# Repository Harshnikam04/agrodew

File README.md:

<div align="center">
  <h1>🌱 Agrodew</h1>
  <p>An end-to-end smart agriculture system combining custom IoT hardware, a powerful backend, and a cross-platform mobile application.</p>

  <p>

  </p>
</div>

---

## 📖 Overview

**Agrodew** is a comprehensive solution designed to monitor and manage agricultural data. By deploying custom hardware sensors in the field, data is transmitted to a central backend and displayed in real-time on a mobile application. This empowers farmers and agricultural enthusiasts to make data-driven decisions based on live environmental metrics.

## 🏗️ System Architecture (Monorepo)

This repository contains all three core components of the Agrodew ecosystem:

### 1. `mobile/` 📱
The user-facing mobile application built to provide real-time analytics and controls.
- **Features**: Interactive dashboards, real-time sensor updates, and AI-driven insights (`aiService.js`).
- **Tech**: React Native / Expo.

### 2. `backend/` ⚙️
The core API server that bridges the hardware and the mobile application.
- **Features**: REST API endpoints for receiving data from Arduino/IoT devices, processing sensor readings (Temperature, Humidity, Soil Moisture, Water Level, AQI), and storing them in a Firebase Firestore database.
- **Tech**: Node.js, Express, Firebase Admin SDK.

### 3. `agrodewpcb/` ⚡
The custom-designed Printed Circuit Board (PCB) for data collection.
- **Features**: Integrates multiple sensors and a microcontroller into a single, deployable field unit.
- **Tech**: KiCad 9.0 (Schematics and PCB layouts included).

---

## 🚀 Key Features

- **Real-Time Environmental Monitoring**: Track Temperature, Humidity, Soil Moisture, Water Levels, and Air Quality Index (AQI).
- **IoT Integration**: Direct communication between custom hardware nodes and the cloud backend.
- **AI Analytics**: Intelligent data processing integrated directly into the mobile client.
- **Cloud Database**: Fast, scalable, and secure data storage using Firebase.

---

## 🛠️ Getting Started

To run the project locally, you will need to start both the backend and the mobile app.

### Backend Setup
1. Navigate to the backend directory:
   ```bash
   cd backend
   ```
2. Install dependencies:
   ```bash
   npm install
   ```
3. Ensure you have your Firebase Service Account credentials set up.
4. Start the server:
   ```bash
   npm run dev
   ```

### Mobile Setup
1. Open a new terminal and navigate to the mobile directory:
   ```bash
   cd mobile
   ```
2. Install dependencies:
   ```bash
   npm install
   ```
3. Start the application:
   ```bash
   npm start
   ```

---

## 🤝 Contributing

Contributions are always welcome! Feel free to open an issue or submit a Pull Request if you have suggestions for new features or improvements.

## 📄 License

This project is open-source and available under the [MIT License](LICENSE).

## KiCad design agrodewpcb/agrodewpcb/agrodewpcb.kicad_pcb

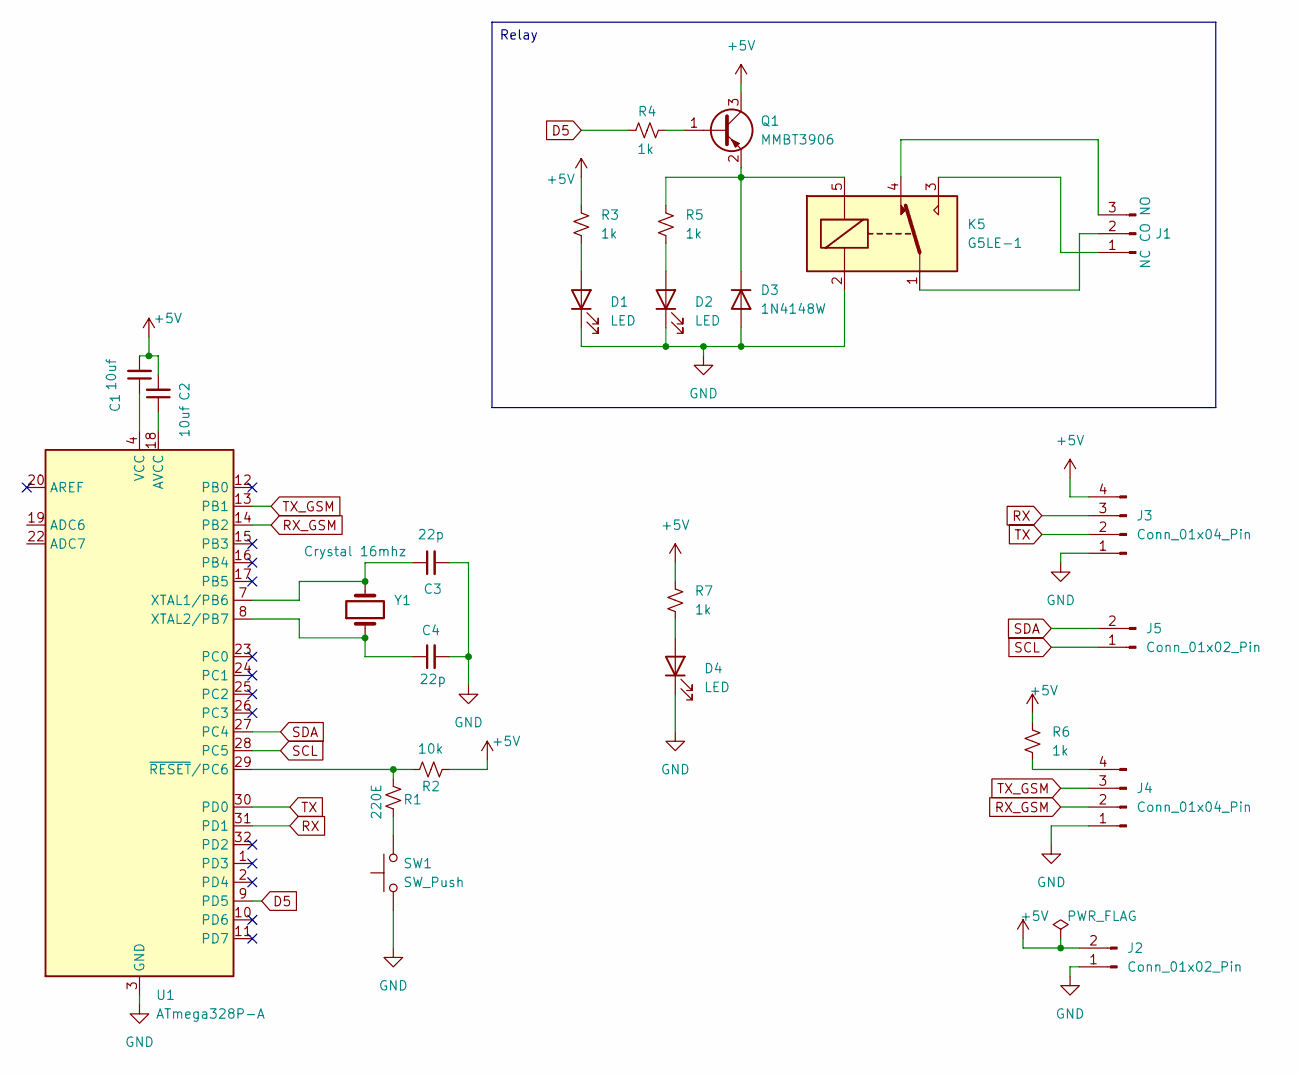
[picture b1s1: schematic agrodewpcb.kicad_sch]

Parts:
C1, C2: 10uf; C_1206_3216Metric_Pad1.33x1.80mm_HandSolder
C3, C4: 22p; C_1206_3216Metric_Pad1.33x1.80mm_HandSolder
D1, D2, D4: LED; LED_1206_3216Metric_Pad1.42x1.75mm_HandSolder
D3: 1N4148W; D_SOD-123
J1: NC CO NO; JST_NV_B03P-NV_1x03_P5.00mm_Vertical
J2, J5: Conn_01x02_Pin; PinHeader_1x02_P2.54mm_Vertical
J3, J4: Conn_01x04_Pin; PinHeader_1x04_P2.54mm_Vertical
K5: G5LE-1; Relay_SPDT_Omron-G5LE-1
Q1: MMBT3906; SOT-23
R1: 220E; R_1206_3216Metric_Pad1.30x1.75mm_HandSolder
R2: 10k; R_1206_3216Metric_Pad1.30x1.75mm_HandSolder
R3, R4, R5, R6, R7: 1k; R_1206_3216Metric_Pad1.30x1.75mm_HandSolder
SW1: SW_Push; SW_Push_1P1T_XKB_TS-1187A
U1: ATmega328P-A; TQFP-32_7x7mm_P0.8mm
Y1: Crystal 16mhz; Crystal_HC49-4H_Vertical

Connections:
+5V: C1.2, C2.2, J2.2, J3.4, Q1.3 (C), R2.2, R3.1, R6.1, R7.1
D5: R4.1, U1.9 (PD5)
GND: C3.2, C4.2, D1.1 (K), D2.1 (K), D3.2 (A), D4.1 (K), J2.1, J3.1, J4.1, K5.2, SW1.1, U1.3 (GND), U1.5 (GND), U1.21 (GND)
unnamed: C1.1, U1.4 (VCC), U1.6 (VCC)
unnamed: D1.2 (A), R3.2
unnamed: D2.2 (A), R5.2
unnamed: D3.1 (K), K5.5, Q1.2 (E), R5.1
unnamed: D4.2 (A), R7.2
unnamed: J1.1, K5.3
unnamed: J1.2, K5.1
unnamed: J1.3, K5.4
unnamed: J4.4, R6.2
unnamed: Q1.1 (B), R4.2
unnamed: R1.2, SW1.2
unnamed: C2.1, U1.18 (AVCC)
unnamed: C3.1, U1.7 (XTAL1/PB6), Y1.2
unnamed: C4.1, U1.8 (XTAL2/PB7), Y1.1
unnamed: R1.1, R2.1, U1.29 (~RESET/PC6)
RX: J3.3, U1.31 (PD1)
RX_GSM: J4.2, U1.14 (PB2)
SCL: J5.1, U1.28 (PC5)
SDA: J5.2, U1.27 (PC4)
TX: J3.2, U1.30 (PD0)
TX_GSM: J4.3, U1.13 (PB1)

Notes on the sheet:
Relay

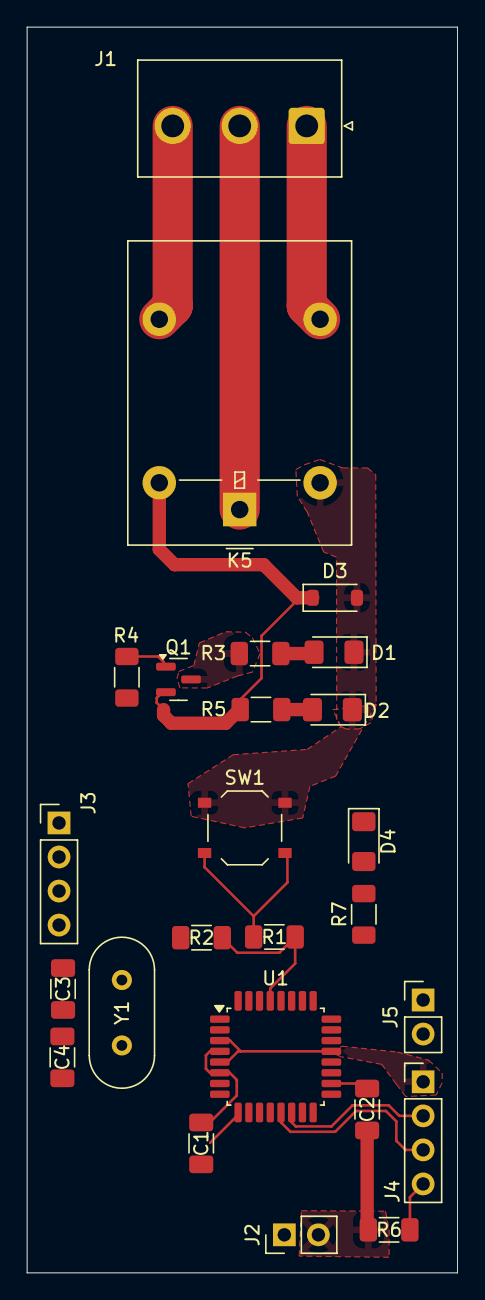
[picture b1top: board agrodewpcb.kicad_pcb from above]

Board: 2 copper layers, 32.1 x 93.0 mm, 25 parts (0 on the bottom side), 24 nets.

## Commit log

2026-04-22 Initial commit: Add Agrodew backend and mobile app
2026-04-22 Fix: rename app to Agrodew, update package name
2026-04-22 Fix: use @expo/vector-icons, fix firebase auth import for EAS build
2026-04-22 Fix: add async-storage for firebase auth persistence, update app icons
2026-04-22 Optimize: add expo-build-properties to shrink Android APK size
2026-05-11 Initial commit: combined mobile and backend into a monorepo
2026-05-11 Add comprehensive README for monorepo
